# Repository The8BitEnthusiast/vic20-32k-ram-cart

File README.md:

# A 32K RAM Expansion PCB and 3D Printed Cart for the VIC-20

After building Ben Eater's 6502 breadboard computer, I undertook this project to see how hard it would be to upgrade the RAM of my VIC-20. After all, the VIC-20 is basically a BE6502 in a case with a video chip and a keyboard. This was also an opportunity to learn how expansion cartridges are designed.

## The Starting Point

I didn't want to start this project from scratch, so I looked around for prior designs. I eventually landed on this elegant [2-chip memory expansion design](http://www.zimmers.net/anonftp/pub/cbm/documents/projects/memory/vic20/32kB.html) from Adam Bergstrom. Absolutely brilliant. As the diagram below shows, there are 4 8K blocks of memory that are empty and available for expansion on the stock machine. There is also an additional 3K of RAM available, but I have opted to not exploit that so I stuck to a single 32K SRAM chip design.

The diagram also shows how each available memory block is already decoded on the expansion port with 7 active-low chip select signals. 4 for each of the 8K blocks, and 3 for each 1K block in lower RAM. Adam's design exploits that by using a priority encoder, the 74LS147, to encode the chip-select lines into a 2-bit number that is fed to address pins A14 and A13 of the RAM chip. I had a 74LS148 priority encoder on hand, so I adjusted the design slightly to take into account the small differences.

## KiCAD Schematics

The schematics for the design is shown below. It is essentially a translation of Adam's design, with the minor modifications described above. For this project, one of my goals was to learn how to model an edge connector. As it happens, there is an excellent [tutorial for creating a C64 cartridge on Youtube](https://www.youtube.com/watch?v=8ikvcYKftms). All I had to do was adapt the specifications to the VIC-20 expansion port's pin pitch and dimensions. 

## PCB Design

As I already had gained some exposure to PCB design through other tutorials, creating the PCB for this cartridge was relatively straighforward. The new knowledge I gained from the video tutorial referenced in the previous section was how to create a custom footprint. That was a great skill to acquire!

## Assembly

For this project I received some special brotherly help to get a cartridge shell 3D printed. The result was impressive, it was a precise match for the PCB!

## Final Outcome

So there you have it, a homemade 32k ram expander. I plugged the cartridge in, and voilà, I was greeted with 28,159 bytes free, woohoo! ...now wait a minute (moment of panic), that's not 32K + 3, there is a whole 8K missing! After some research, I learned that memory block 5 is not counted by Basic! All good, a few POKEs and PEEKs confirmed the availability of that 8K block!

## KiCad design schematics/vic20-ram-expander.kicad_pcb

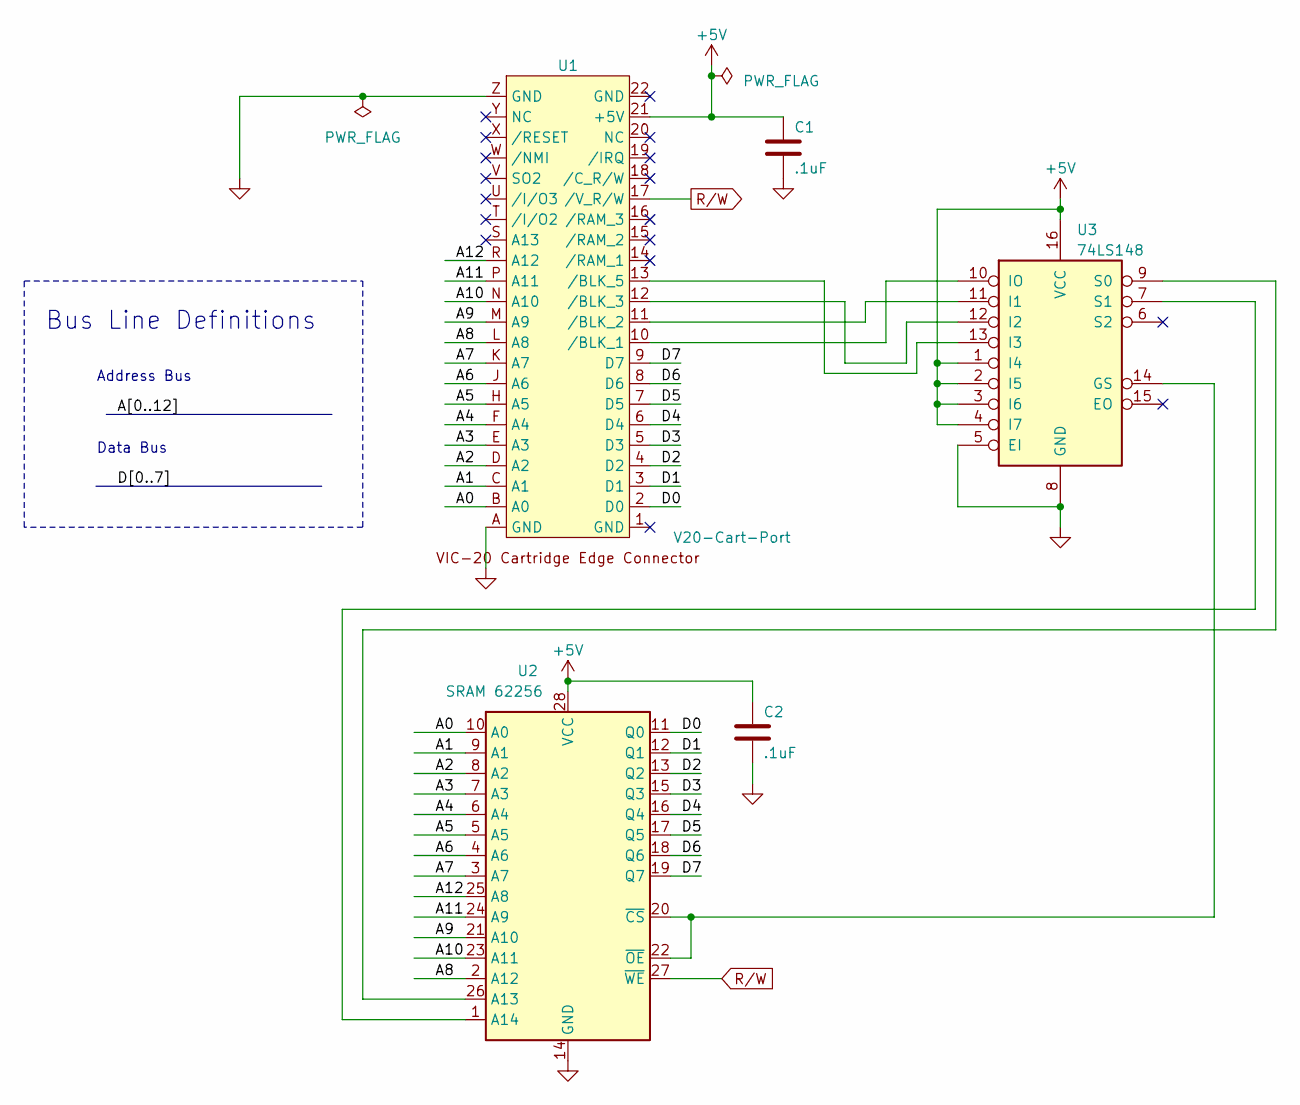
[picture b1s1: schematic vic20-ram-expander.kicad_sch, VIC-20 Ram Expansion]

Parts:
C1, C2: .1uF; C_Disc_D5.0mm_W2.5mm_P5.00mm
U1: V20-Cart-Port; VIC20-Expansion-Port
U2: SRAM 62256; DIP-28_W15.24mm
U3: 74LS148; DIP-16_W7.62mm

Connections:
+5V: C1.1, C2.1, U1.21 (+5V), U2.28 (VCC), U3.1 (I4), U3.2 (I5), U3.3 (I6), U3.4 (I7), U3.16 (VCC)
/A0: U1.B (A0), U2.10 (A0)
/A1: U1.C (A1), U2.9 (A1)
/A2: U1.D (A2), U2.8 (A2)
/A3: U1.E (A3), U2.7 (A3)
/A4: U1.F (A4), U2.6 (A4)
/A5: U1.H (A5), U2.5 (A5)
/A6: U1.J (A6), U2.4 (A6)
/A7: U1.K (A7), U2.3 (A7)
/A8: U1.L (A8), U2.2 (A12)
/A9: U1.M (A9), U2.21 (A10)
/A10: U1.N (A10), U2.23 (A11)
/A11: U1.P (A11), U2.24 (A9)
/A12: U1.R (A12), U2.25 (A8)
/D0: U1.2 (D0), U2.11 (Q0)
/D1: U1.3 (D1), U2.12 (Q1)
/D2: U1.4 (D2), U2.13 (Q2)
/D3: U1.5 (D3), U2.15 (Q3)
/D4: U1.6 (D4), U2.16 (Q4)
/D5: U1.7 (D5), U2.17 (Q5)
/D6: U1.8 (D6), U2.18 (Q6)
/D7: U1.9 (D7), U2.19 (Q7)
GND: C1.2, C2.2, U1.A (GND), U1.Z (GND), U2.14 (GND), U3.5 (EI), U3.8 (GND)
unnamed: U1.10 (/BLK_1), U3.10 (IO)
unnamed: U1.11 (/BLK_2), U3.11 (I1)
unnamed: U1.12 (/BLK_3), U3.12 (I2)
unnamed: U1.13 (/BLK_5), U3.13 (I3)
unnamed: U2.26 (A13), U3.9 (S0)
unnamed: U2.1 (A14), U3.7 (S1)
unnamed: U2.20 (~CS), U2.22 (~OE), U3.14 (GS)
R/W: U1.17 (/V_R/W), U2.27 (~WE)

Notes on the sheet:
Address Bus
Bus Line Definitions
Data Bus

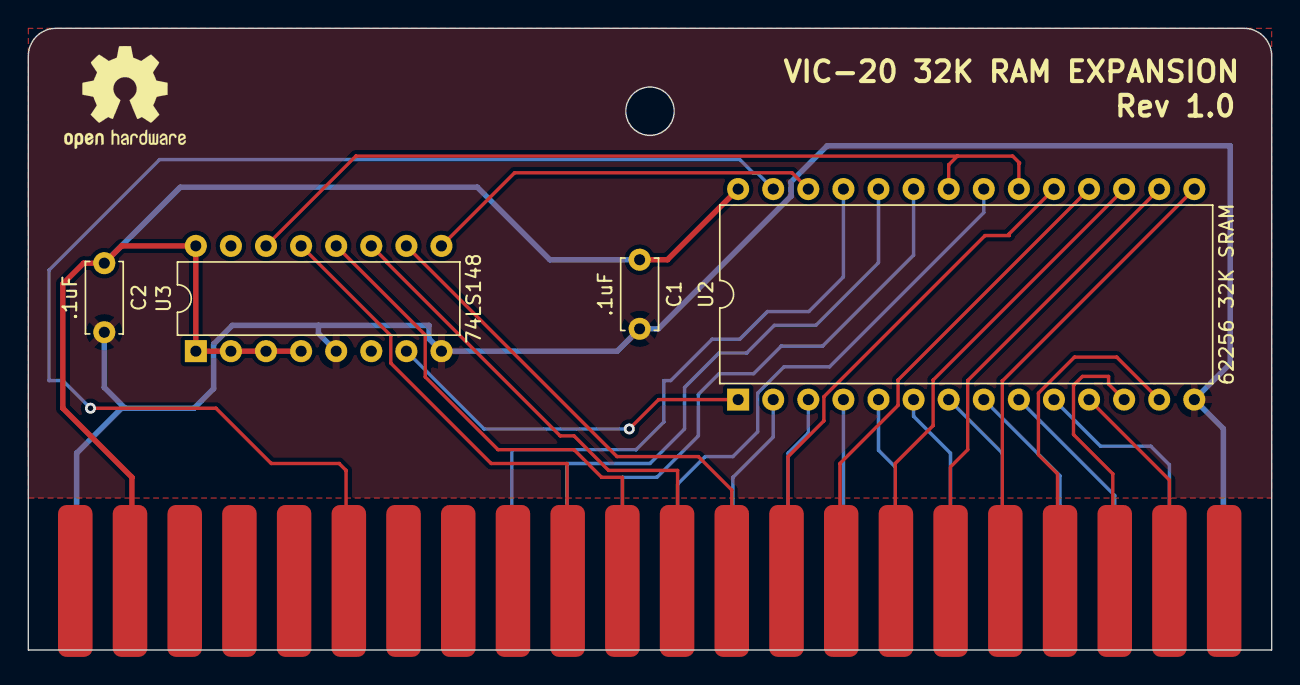
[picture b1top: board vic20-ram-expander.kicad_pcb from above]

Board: 2 copper layers, 90.0 x 45.0 mm, 5 parts (0 on the bottom side), 31 nets.

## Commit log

2023-06-08 initial upload
2023-06-08 minor updates
2023-06-08 added schematics pdf
2023-06-08 fixed typo
